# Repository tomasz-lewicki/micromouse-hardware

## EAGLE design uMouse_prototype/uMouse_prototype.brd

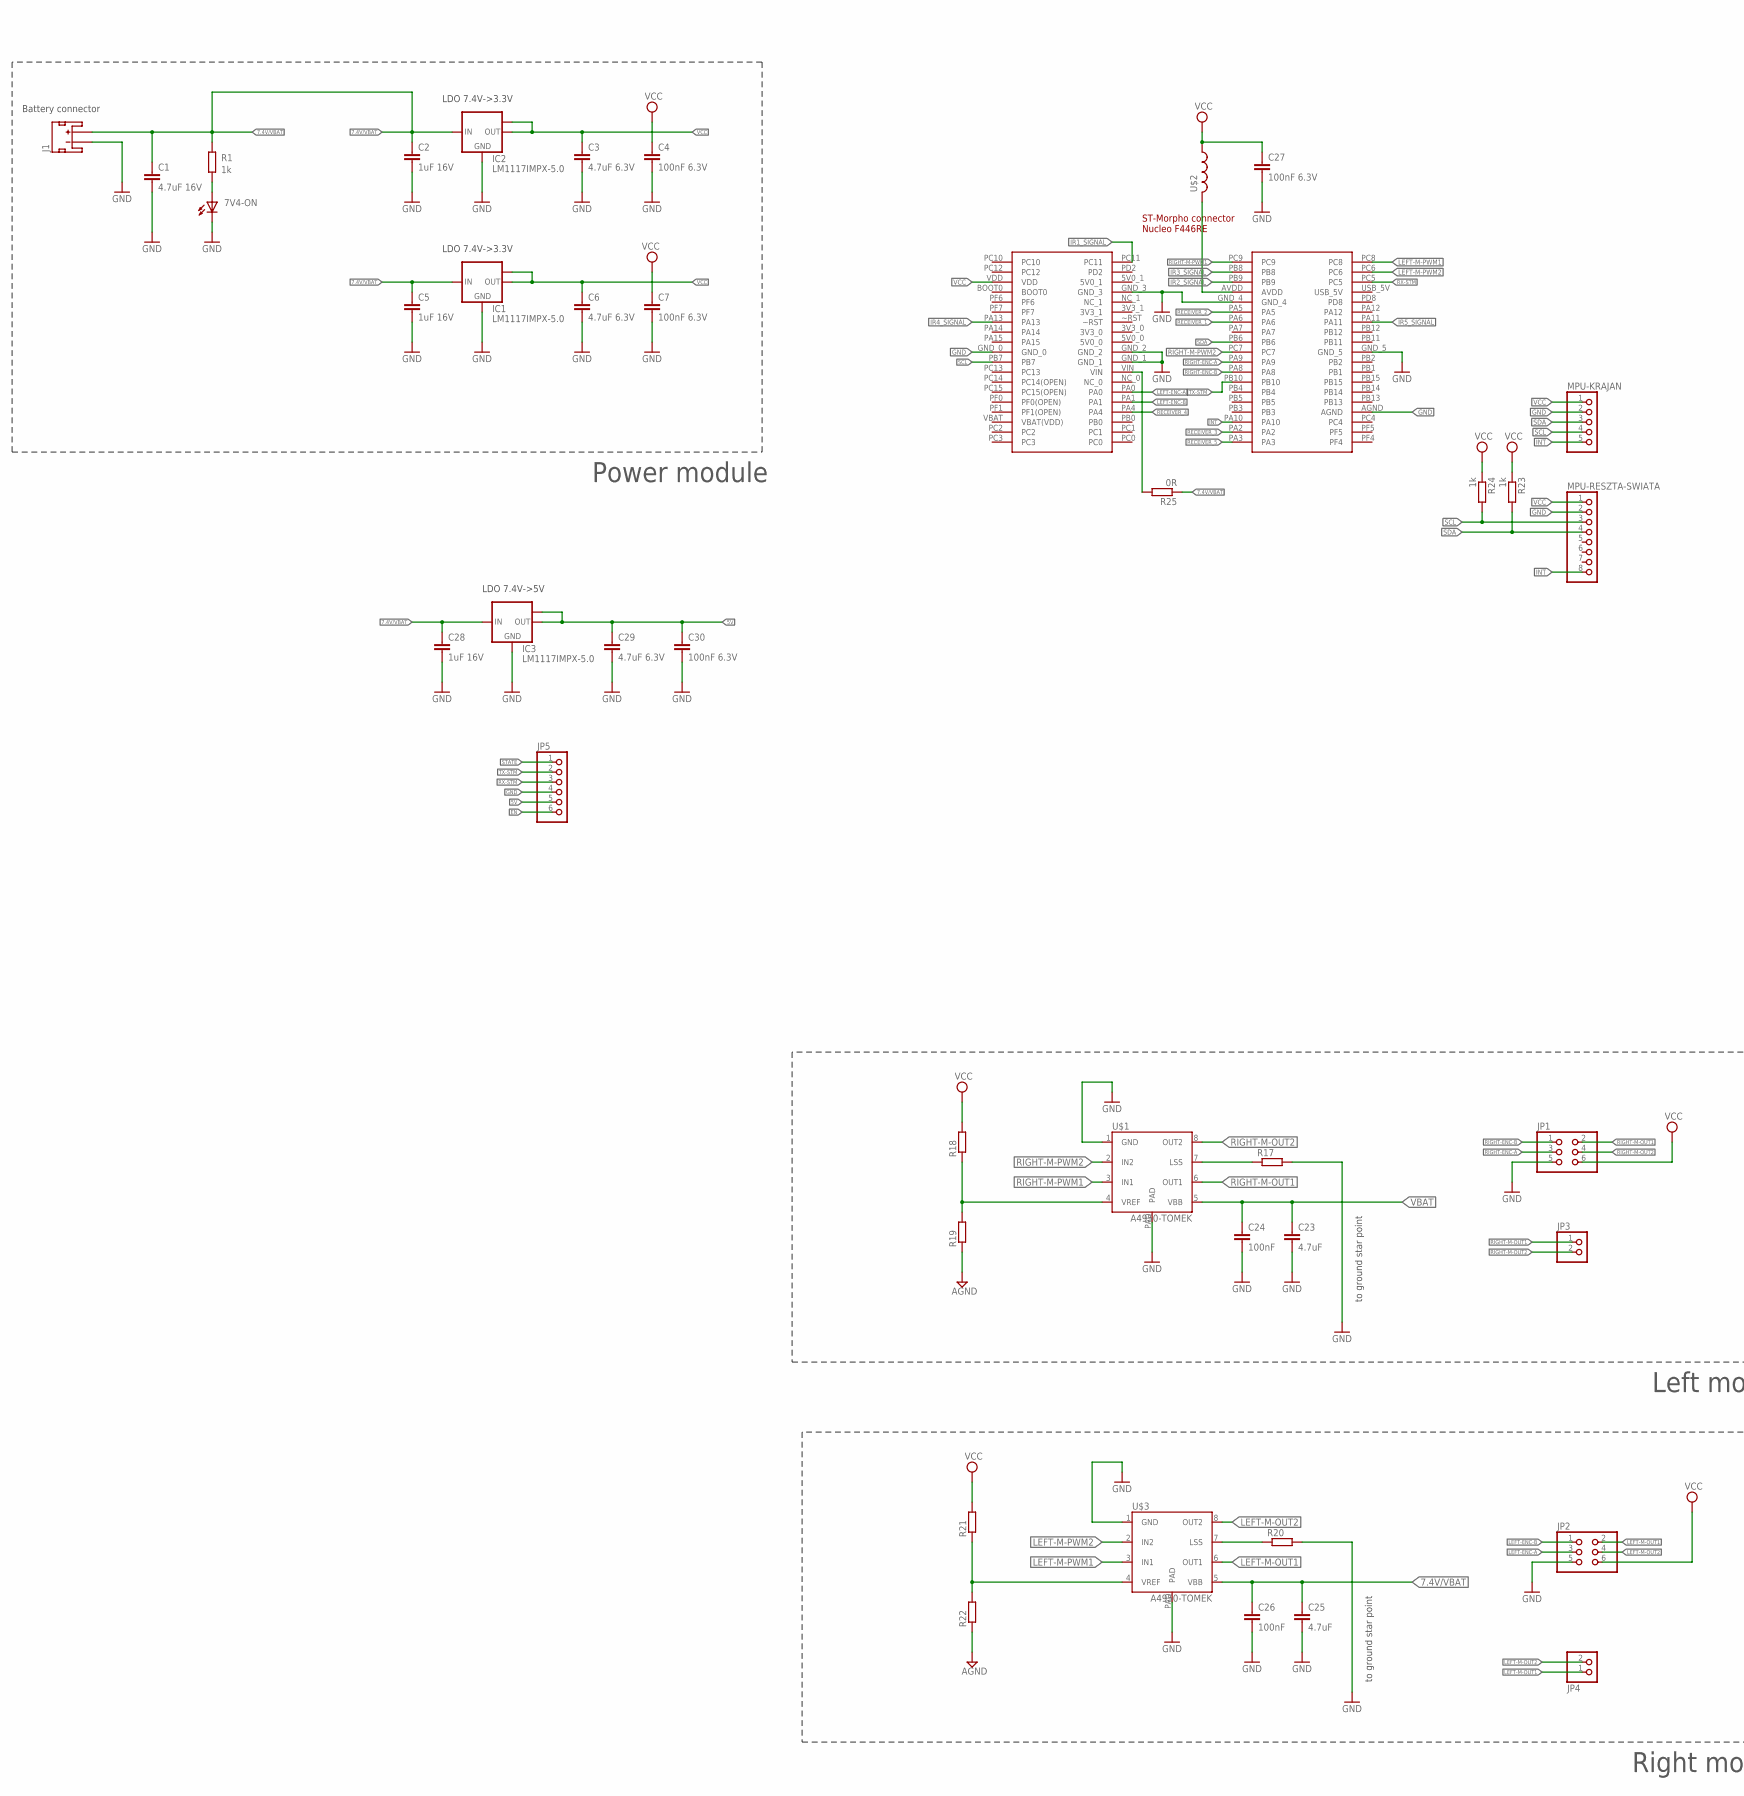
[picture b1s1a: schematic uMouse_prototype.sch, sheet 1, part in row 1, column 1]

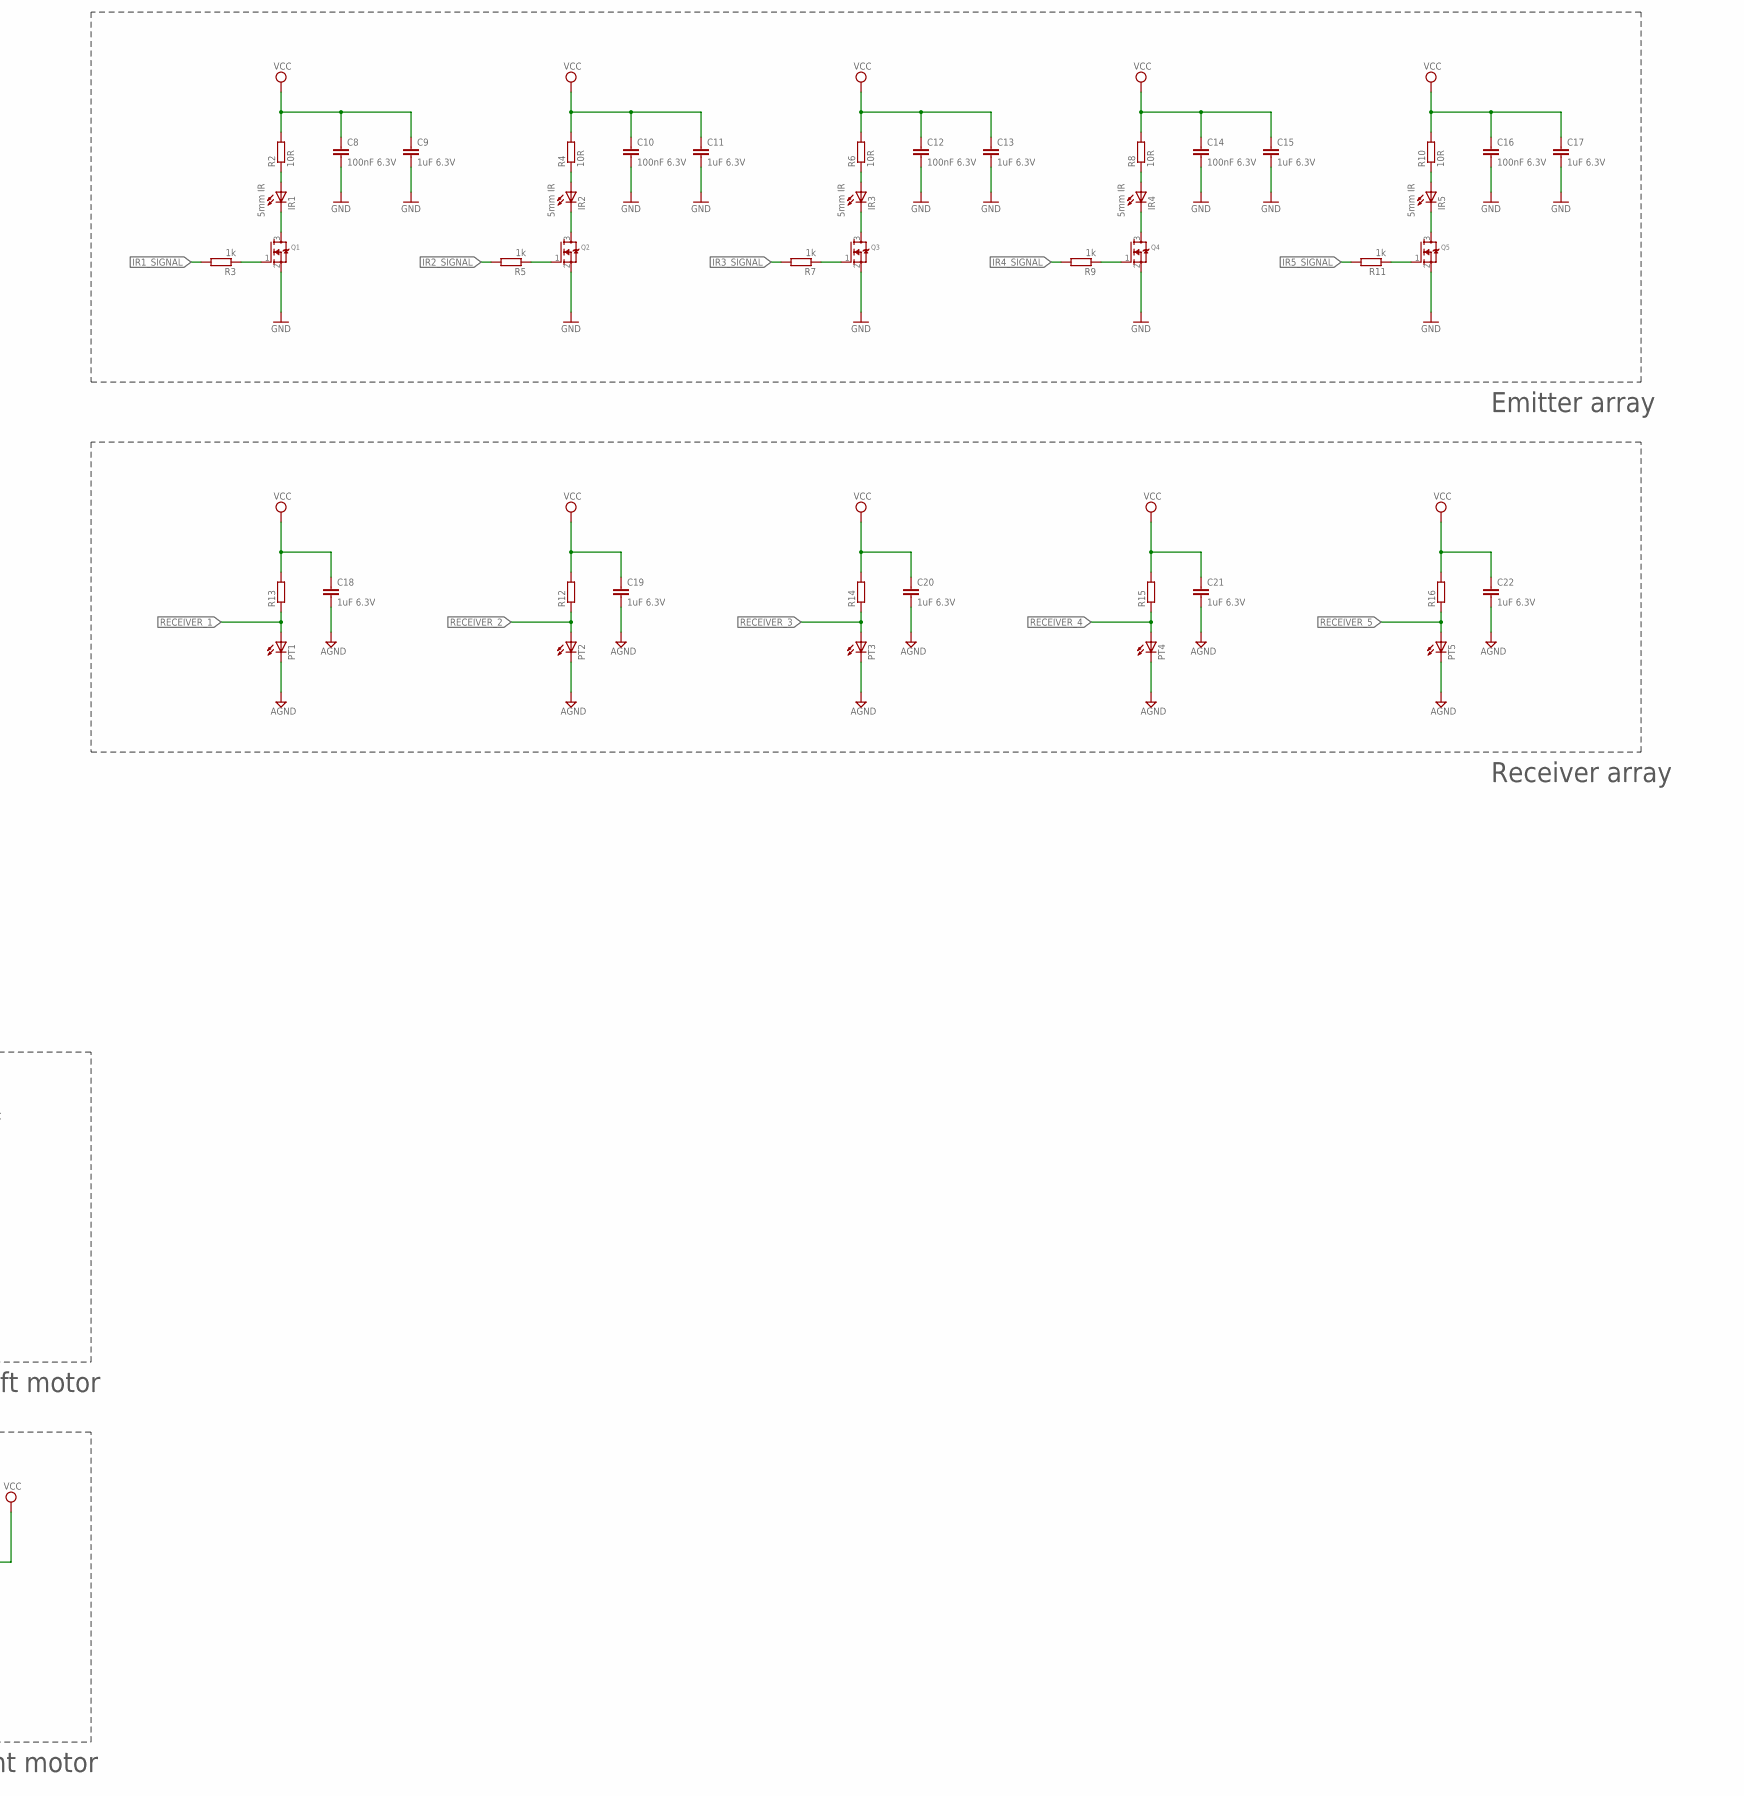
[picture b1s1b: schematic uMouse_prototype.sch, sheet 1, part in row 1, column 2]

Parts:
7V4-ON: LEDCHIP-LED0805; CHIP-LED0805
C1: 4.7uF 16V; C0805K
C2, C5, C28: 1uF 16V; C0805K
C3, C6, C29: 4.7uF 6.3V; C0805K
C4, C7, C8, C10, C12, C14, C16, C27, C30: 100nF 6.3V; C0805K
C9, C11, C13, C15, C17, C18, C19, C20, C21, C22: 1uF 6.3V; C0805K
C23, C25: 4.7uF; C0805K
C24, C26: 100nF; C0805K
IC1, IC2, IC3: LM1117IMPX-5.0; SOT223
IR1, IR2, IR3, IR4, IR5: 5mm IR; LED5MM
J1: JST_2MM_MALE; JST-2-SMD
JP1, JP2: PINHD-2X3; 2X03
JP3, JP4: PINHD-1X2; 1X02
JP5: PINHD-1X6; 1X06
MPU-KRAJAN: PINHD-1X5; 1X05
MPU-RESZTA-SWIATA: PINHD-1X8; 1X08
PT1, PT2, PT3, PT4, PT5: LED3MM
Q1, Q2, Q3, Q4, Q5: MOSFET-NREFLOW; SOT23
R1: 1k; R0805
R2, R4, R6, R8, R10: 10R; M0805
R3, R5, R7, R9, R11, R23, R24: 1k; M0805
R12, R13, R14, R15, R16, R18, R19, R21, R22: R-EU_R0805; R0805
R17, R20: R-EU_R2512; R2512
R25: 0R; M0805
U$1, U$3: A4950-TOMEK; SOIC8TP
U$2: INDUCTOR_0805_L; RESC0805_L
U$5: ST_MORPHO_STM32_F446RE; MORPHO-4X19

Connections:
5V: C29.1, C30.1, IC3.2 (OUT), IC3.TAB (OUT1), JP5.5
7.4V/VBAT: C1.1, C2.1, C5.1, C25.1, C26.1, C28.1, IC1.3 (IN), IC2.3 (IN), IC3.3 (IN), J1.2 (+), R1.2, R25.1, U$3.5 (VBB)
EN: JP5.6
GND: 7V4-ON.C, C1.2, C2.2, C3.2, C4.2, C5.2, C6.2, C7.2, C8.2, C9.2, C10.2, C11.2, C12.2, C13.2, C14.2, C15.2, C16.2, C17.2, C18.2, C19.2, C20.2, C21.2, C22.2, C23.2, C24.2, C25.2, C26.2, C27.2, C28.2, C29.2, C30.2, IC1.1 (GND), IC2.1 (GND), IC3.1 (GND), J1.1 (-), JP1.5, JP2.5, JP5.4, MPU-KRAJAN.2, MPU-RESZTA-SWIATA.2, PT1.K (C), PT2.K (C), PT3.K (C), PT4.K (C), PT5.K (C), Q1.2 (S), Q2.2 (S), Q3.2 (S), Q4.2 (S), Q5.2 (S), R17.2, R19.1, R20.2, R22.1, U$1.1 (GND), U$1.PAD, U$3.1 (GND), U$3.PAD, U$5.AGND, U$5.GND_0, U$5.GND_1, U$5.GND_2, U$5.GND_3, U$5.GND_4, U$5.GND_5
INT: MPU-KRAJAN.5, MPU-RESZTA-SWIATA.8, U$5.PA10
IR1_SIGNAL: R3.2, U$5.PC11
IR2_SIGNAL: R5.2, U$5.PB9
IR3: IR3.K (C), Q3.3 (D)
IR3_SIGNAL: R7.2, U$5.PB8
IR4_SIGNAL: R9.2, U$5.PA13
IR5_SIGNAL: R11.2, U$5.PA11
LEFT-ENC-A: JP2.3, U$5.PA0
LEFT-ENC-B: JP2.1, U$5.PA1
LEFT-M-OUT1: JP2.2, JP4.1, U$3.6 (OUT1)
LEFT-M-OUT2: JP2.4, JP4.2, U$3.8 (OUT2)
LEFT-M-PWM1: U$3.3 (IN1), U$5.PC8
LEFT-M-PWM2: U$3.2 (IN2), U$5.PC6
unnamed: 7V4-ON.A, R1.1
unnamed: Q1.1 (G), R3.1
unnamed: IR1.A, R2.1
unnamed: IR1.K (C), Q1.3 (D)
unnamed: Q2.1 (G), R5.1
unnamed: IR2.A, R4.1
unnamed: IR2.K (C), Q2.3 (D)
unnamed: Q3.1 (G), R7.1
unnamed: IR3.A, R6.1
unnamed: Q4.1 (G), R9.1
unnamed: IR4.A, R8.1
unnamed: IR4.K (C), Q4.3 (D)
unnamed: Q5.1 (G), R11.1
unnamed: IR5.A, R10.1
unnamed: IR5.K (C), Q5.3 (D)
unnamed: R17.1, U$1.7 (LSS)
unnamed: R18.1, R19.2, U$1.4 (VREF)
unnamed: R20.1, U$3.7 (LSS)
unnamed: R21.1, R22.2, U$3.4 (VREF)
unnamed: U$2.2, U$5.AVDD
unnamed: R25.2, U$5.VIN
RECEIVER_1: PT1.A, R13.1, U$5.PA6
RECEIVER_2: PT2.A, R12.1, U$5.PA5
RECEIVER_3: PT3.A, R14.1, U$5.PA2
RECEIVER_4: PT4.A, R15.1, U$5.PA4
RECEIVER_5: PT5.A, R16.1, U$5.PA3
RIGHT-ENC-A: JP1.3, U$5.PA9
RIGHT-ENC-B: JP1.1, U$5.PA8
RIGHT-M-OUT1: JP1.2, JP3.1, U$1.6 (OUT1)
RIGHT-M-OUT2: JP1.4, JP3.2, U$1.8 (OUT2)
RIGHT-M-PWM1: U$1.3 (IN1), U$5.PC9
RIGHT-M-PWM2: U$1.2 (IN2), U$5.PC7
RX-STM: JP5.3, U$5.PC5
SCL: MPU-KRAJAN.4, MPU-RESZTA-SWIATA.3, R24.2, U$5.PB7
SDA: MPU-KRAJAN.3, MPU-RESZTA-SWIATA.4, R23.2, U$5.PB6
STATE: JP5.1
TX-STM: JP5.2, U$5.PB10
VBAT: C23.1, C24.1, U$1.5 (VBB)
VCC: C3.1, C4.1, C6.1, C7.1, C8.1, C9.1, C10.1, C11.1, C12.1, C13.1, C14.1, C15.1, C16.1, C17.1, C18.1, C19.1, C20.1, C21.1, C22.1, C27.1, IC1.2 (OUT), IC1.TAB (OUT1), IC2.2 (OUT), IC2.TAB (OUT1), JP1.6, JP2.6, MPU-KRAJAN.1, MPU-RESZTA-SWIATA.1, R2.2, R4.2, R6.2, R8.2, R10.2, R12.2, R13.2, R14.2, R15.2, R16.2, R18.2, R21.2, R23.1, R24.1, U$2.1, U$5.VDD

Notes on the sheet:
Battery connector
LDO 7.4V->3.3V
Power module
Emitter array
Receiver array
to ground star point
Left motor
Right motor
LDO 7.4V->5V

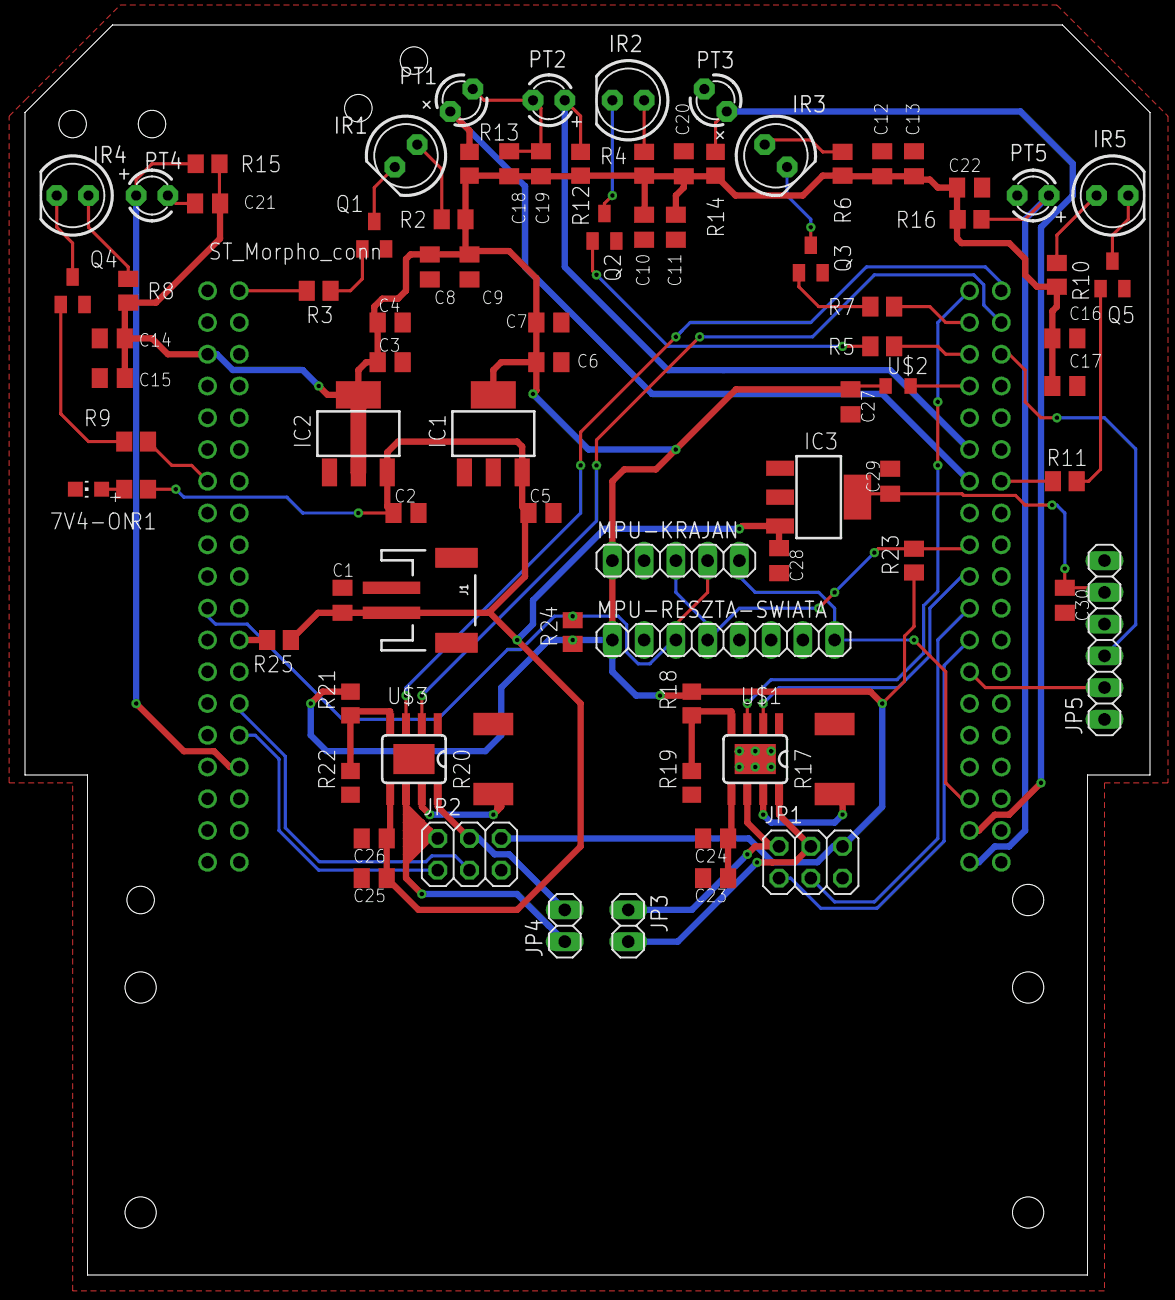
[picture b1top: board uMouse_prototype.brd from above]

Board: 2 copper layers, 90.0 x 100.0 mm, 86 parts (0 on the bottom side), 54 nets.

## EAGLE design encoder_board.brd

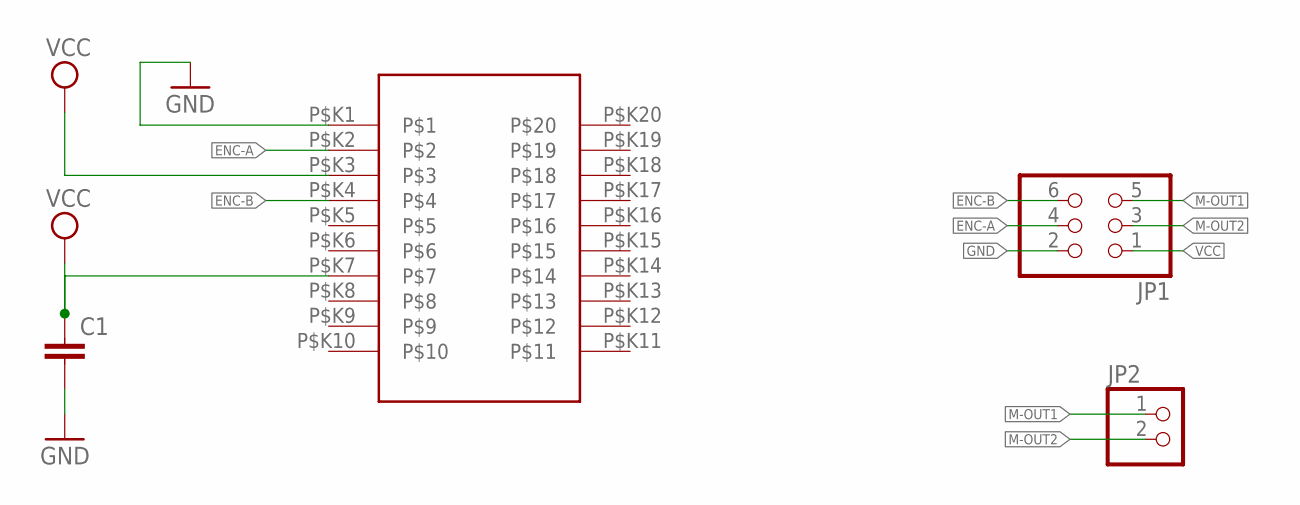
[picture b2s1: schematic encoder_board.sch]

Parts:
C1: C-EUC0805K; C0805K
JP1: PINHD-2X3; 2X03
JP2: PINHD-1X2; 1X02
U$1: TSSOP20

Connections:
ENC-A: JP1.4, U$1.P$K2
ENC-B: JP1.6, U$1.P$K4
GND: C1.2, JP1.2, U$1.P$K1
M-OUT1: JP1.5, JP2.1
M-OUT2: JP1.3, JP2.2
VCC: C1.1, JP1.1, U$1.P$K3, U$1.P$K7

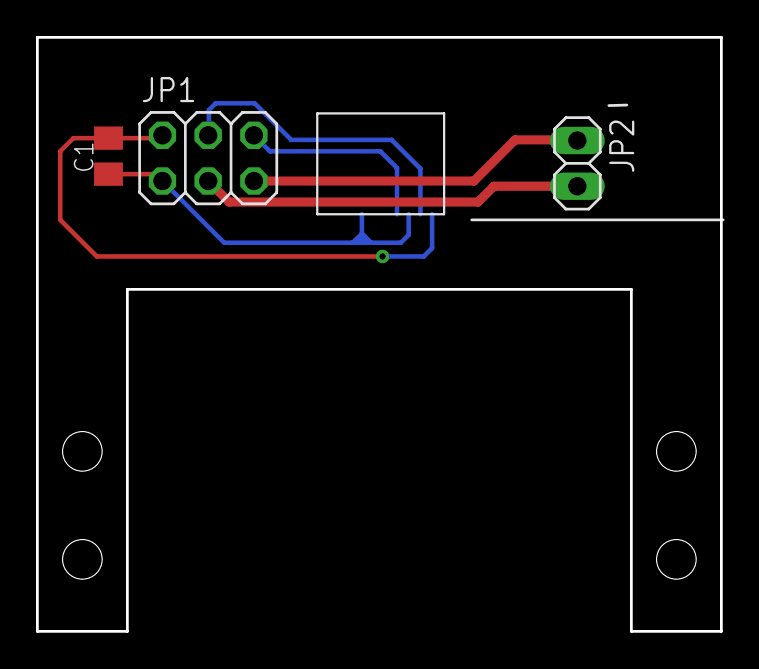
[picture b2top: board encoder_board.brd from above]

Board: 2 copper layers, 38.0 x 33.0 mm, 4 parts (1 on the bottom side), 6 nets.

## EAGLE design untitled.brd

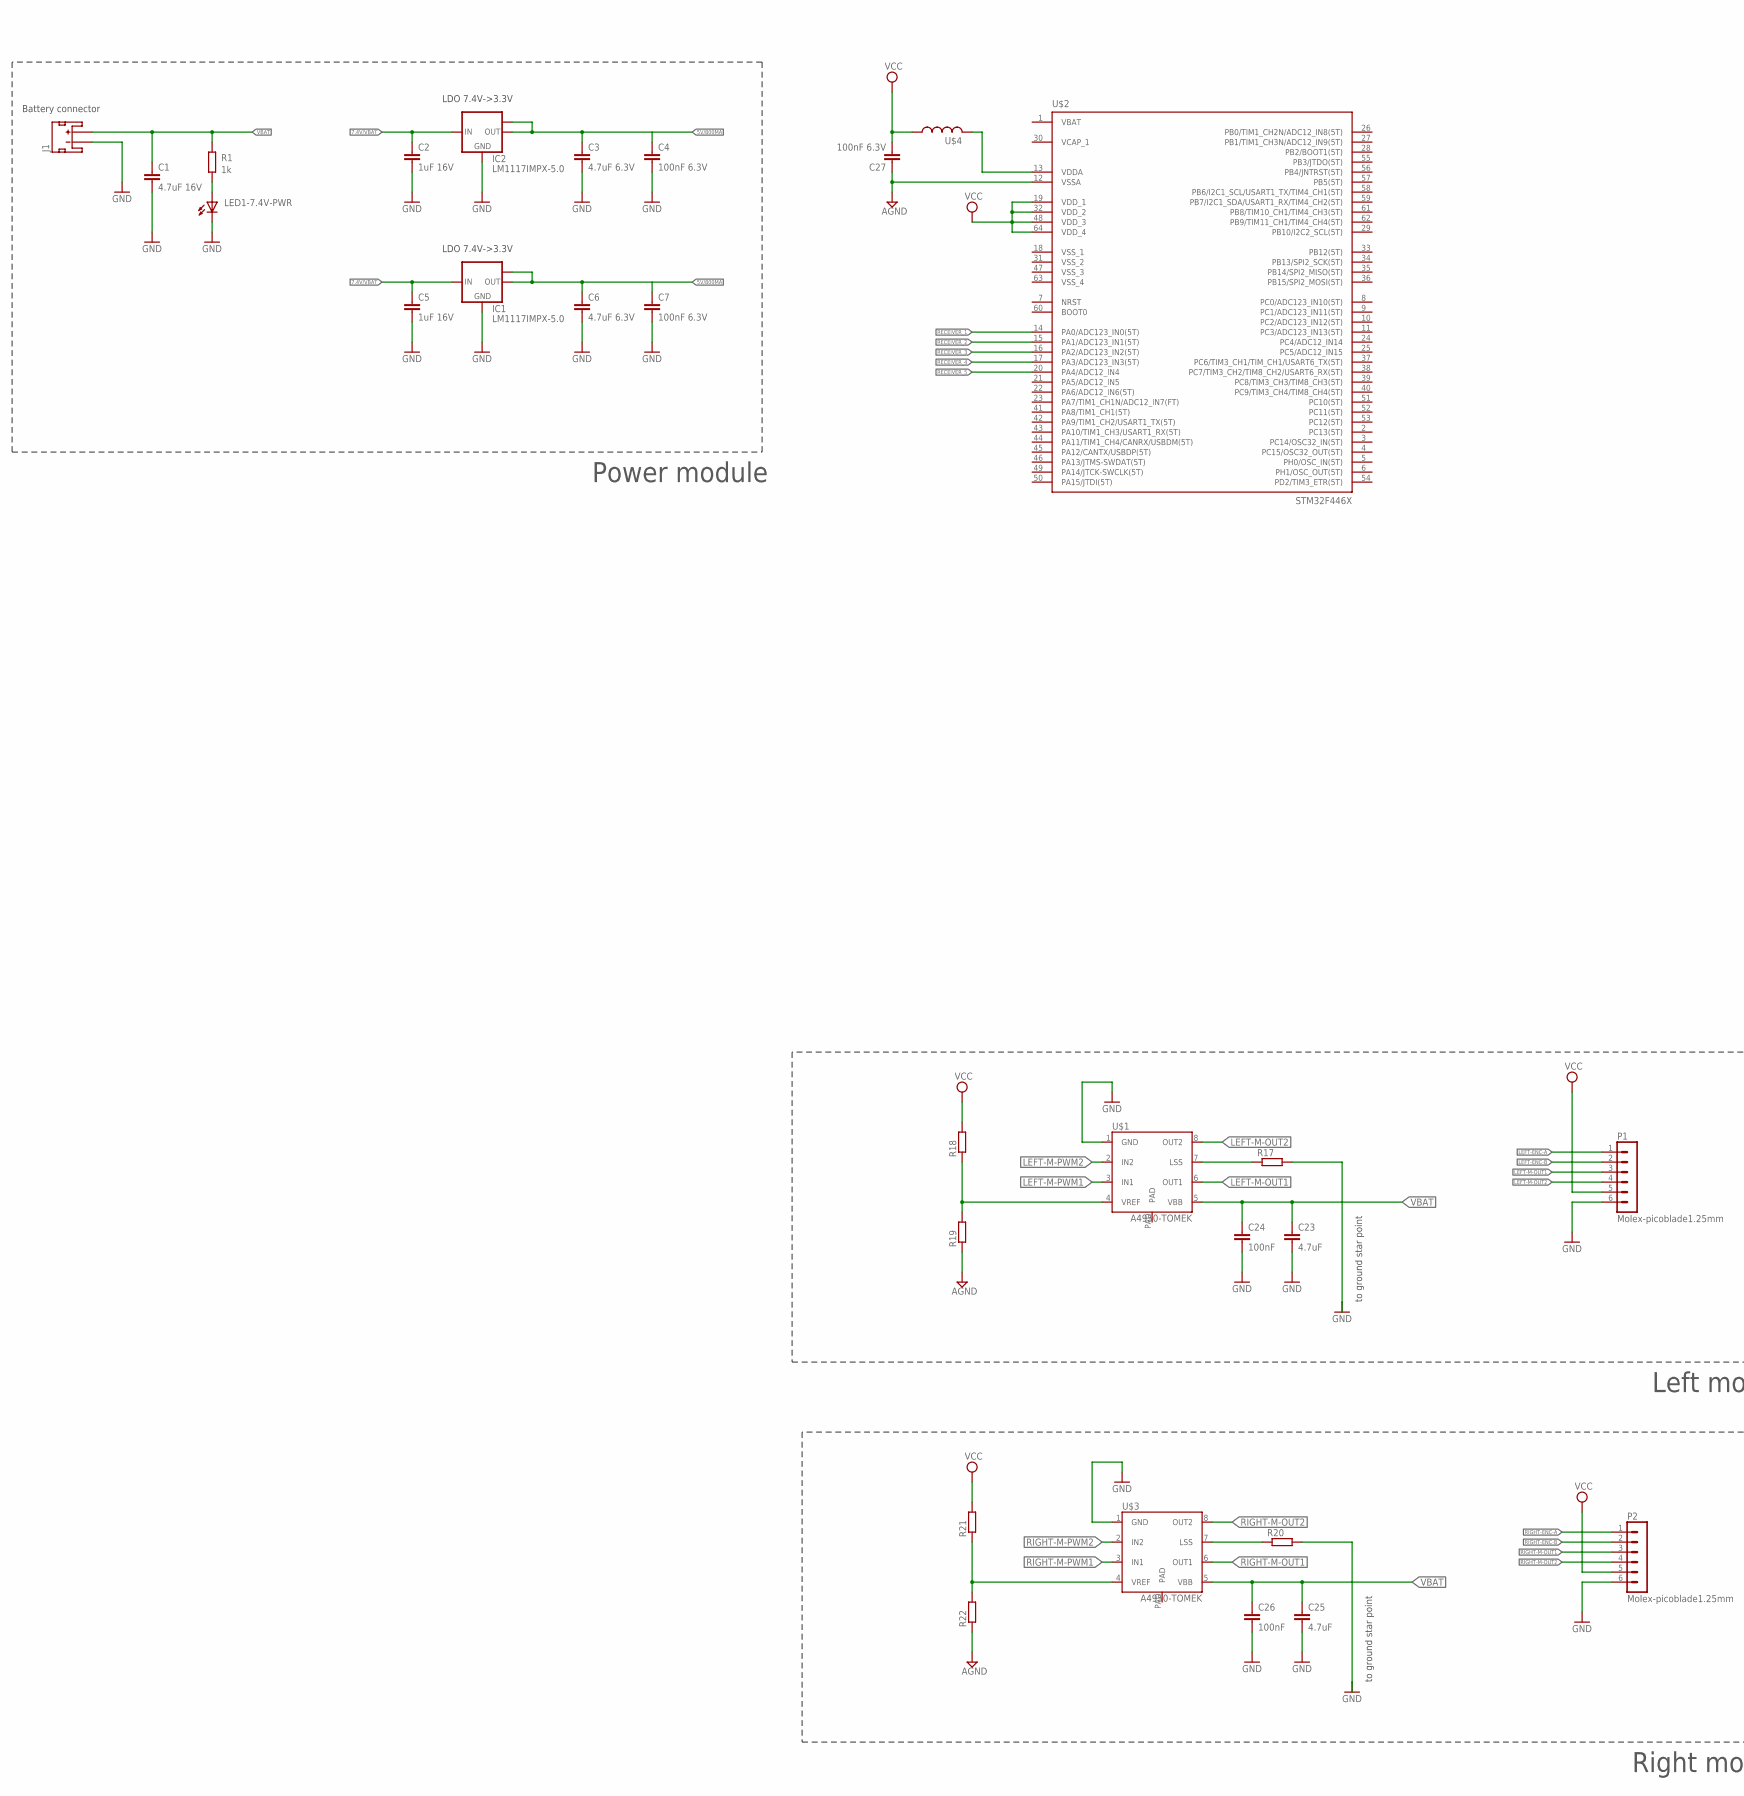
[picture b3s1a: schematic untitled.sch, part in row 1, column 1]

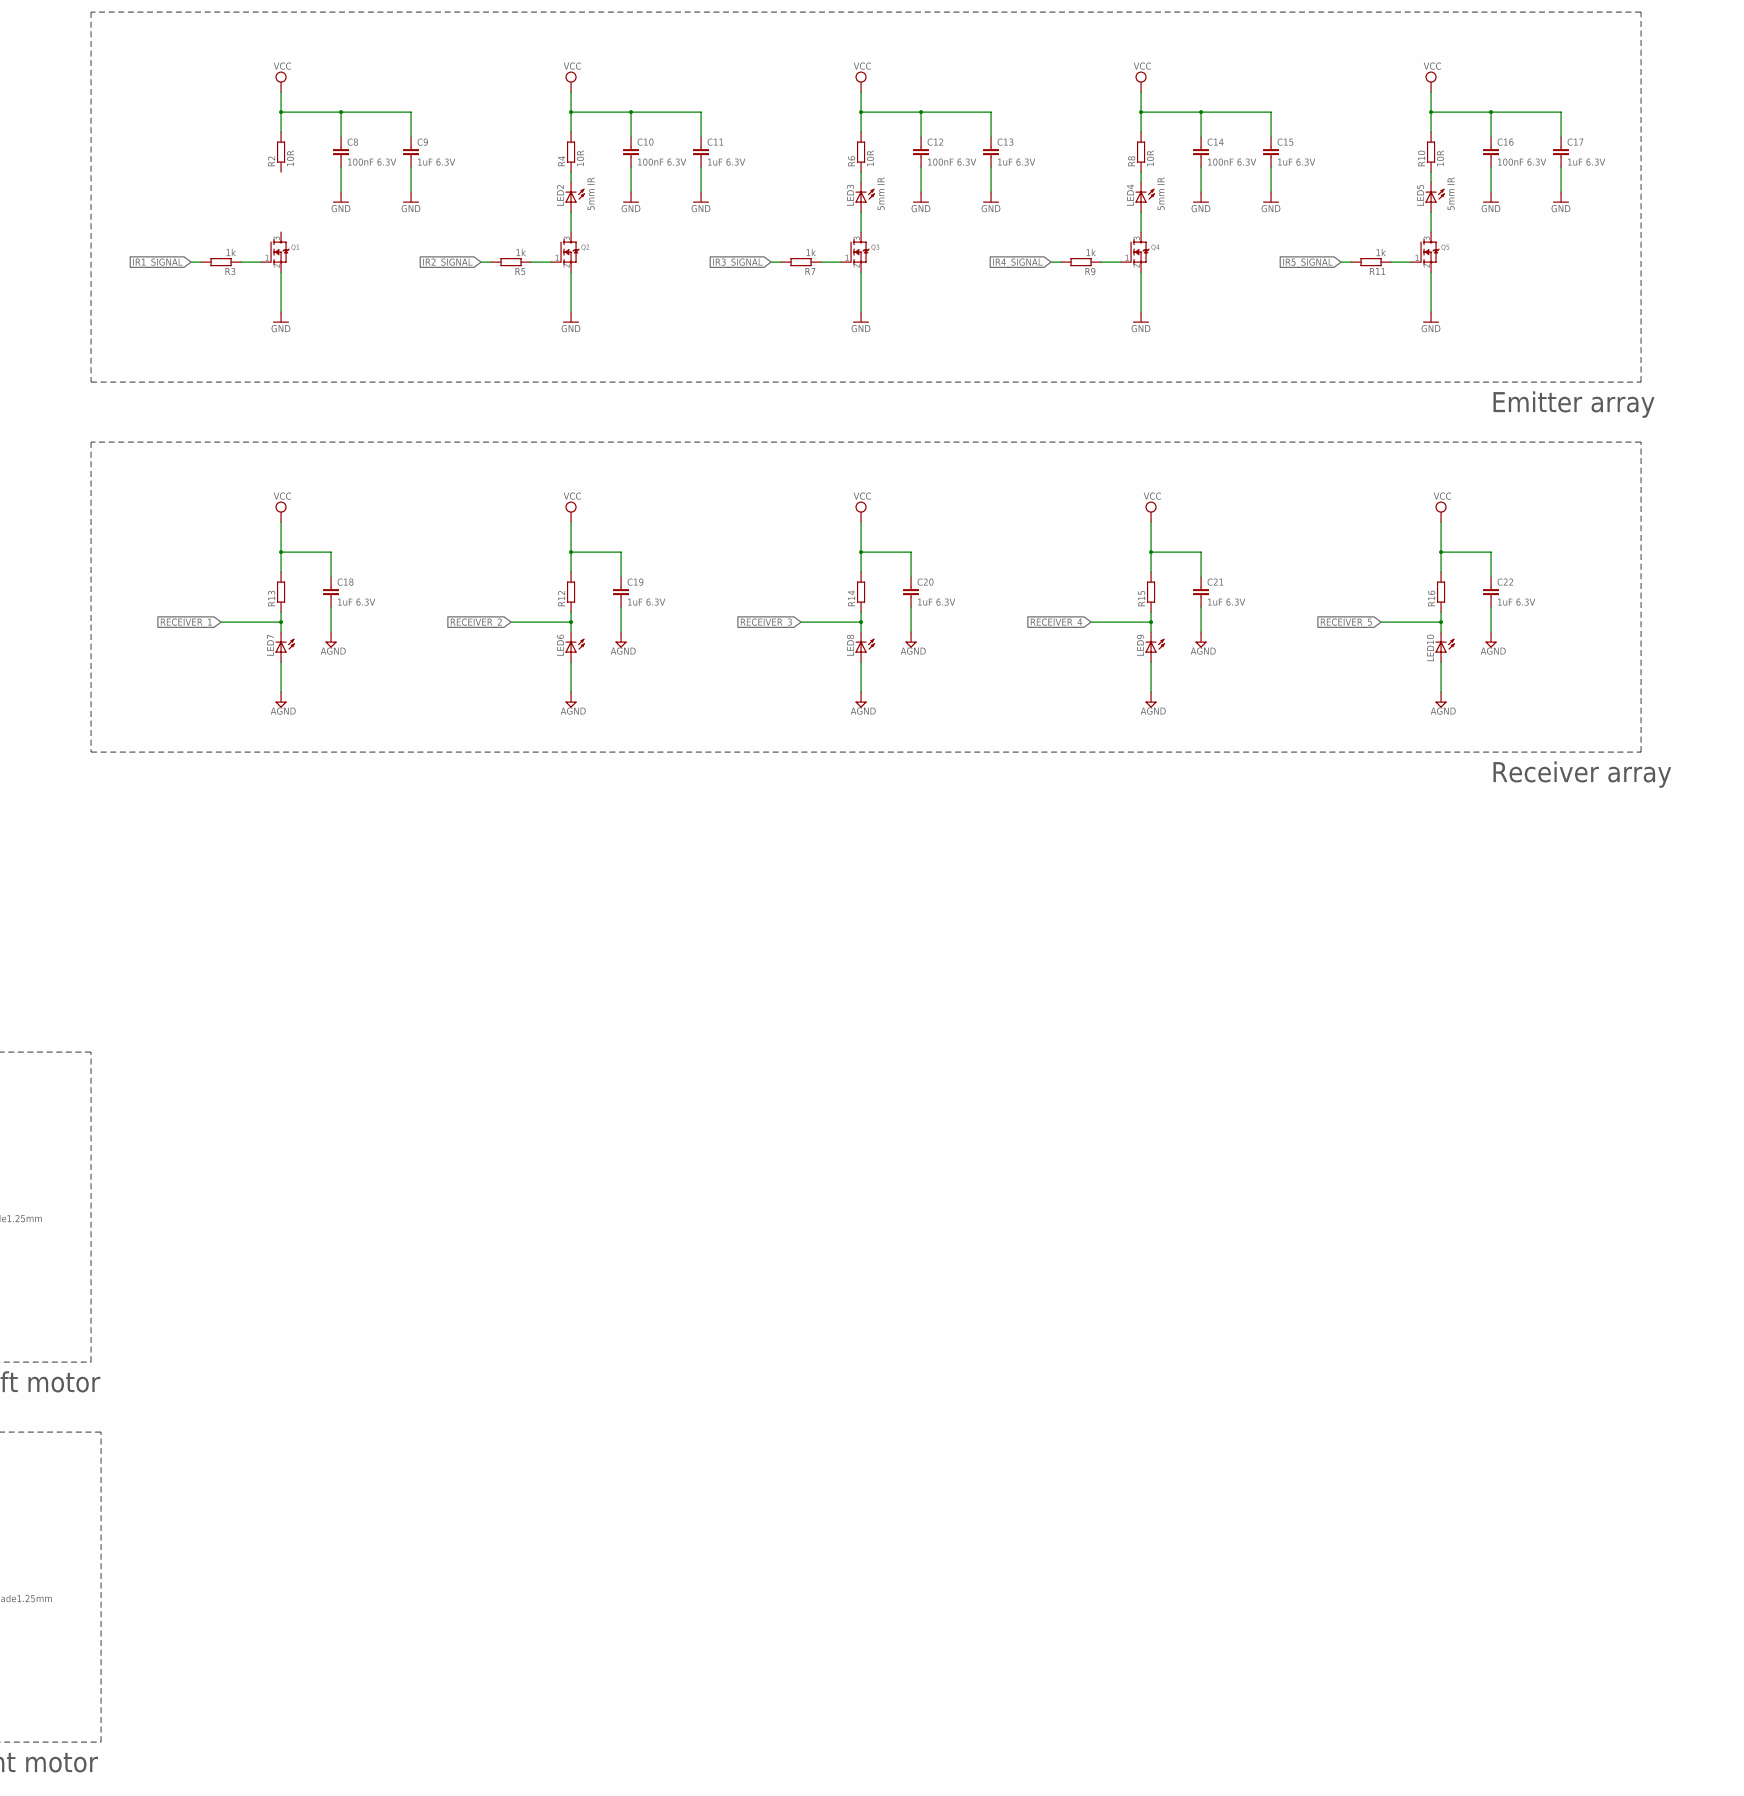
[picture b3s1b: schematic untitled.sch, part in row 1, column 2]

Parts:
C1: 4.7uF 16V; C0805K
C2, C5: 1uF 16V; C0805K
C3, C6: 4.7uF 6.3V; C0805K
C4, C7, C8, C10, C12, C14, C16, C27: 100nF 6.3V; C0805K
C9, C11, C13, C15, C17, C18, C19, C20, C21, C22: 1uF 6.3V; C0805K
C23, C25: 4.7uF; C0805K
C24, C26: 100nF; C0805K
IC1, IC2: LM1117IMPX-5.0; SOT223
J1: JST_2MM_MALE; JST-2-SMD
LED1-7.4V-PWR: LEDCHIP-LED0805; CHIP-LED0805
LED2, LED3, LED4, LED5: 5mm IR; LED5MM
LED6, LED7, LED8, LED9, LED10: LED5MM
P1, P2: Molex-picoblade1.25mm; 53398-0610
Q1, Q2, Q3, Q4, Q5: MOSFET-NREFLOW; SOT23
R1: 1k; R0805
R2, R4, R6, R8, R10: 10R; M0805
R3, R5, R7, R9, R11: 1k; M0805
R12, R13, R14, R15, R16, R18, R19, R21, R22: R-EU_R0805; R0805
R17, R20: R-EU_R2512; R2512
U$1, U$3: A4950-TOMEK; SOIC8TP
U$2: STM32F446X; TQFP64
U$4: INDUCTOR_0805_L; RESC0805_L

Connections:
5V/800MA: C3.1, C6.1, IC1.2 (OUT), IC1.TAB (OUT1), IC2.2 (OUT), IC2.TAB (OUT1)
5V/800MA1: C4.1
5V/800MA2: C7.1
7.4V/VBAT: C2.1, C5.1, IC1.3 (IN), IC2.3 (IN)
AGND: C18.2, C19.2, C20.2, C21.2, C22.2, C27.1, LED6.A, LED7.A, LED8.A, LED9.A, LED10.A, R19.1, R22.1, U$2.12 (VSSA)
GND: C1.2, C2.2, C3.2, C4.2, C5.2, C6.2, C7.2, C8.2, C9.2, C10.2, C11.2, C12.2, C13.2, C14.2, C15.2, C16.2, C17.2, C23.2, C24.2, C25.2, C26.2, IC1.1 (GND), IC2.1 (GND), J1.1 (-), LED1-7.4V-PWR.C, P1.6, P2.6, Q1.2 (S), Q2.2 (S), Q3.2 (S), Q4.2 (S), Q5.2 (S), R17.2, R20.2, U$1.1 (GND), U$3.1 (GND)
IR1_SIGNAL: R3.2
IR2_SIGNAL: R5.2
IR3_SIGNAL: R7.2
IR4_SIGNAL: R9.2
IR5_SIGNAL: R11.2
LEFT-ENC-A: P1.1
LEFT-ENC-B: P1.2
LEFT-M-OUT1: P1.3, U$1.6 (OUT1)
LEFT-M-OUT2: P1.4, U$1.8 (OUT2)
LEFT-M-PWM1: U$1.3 (IN1)
LEFT-M-PWM2: U$1.2 (IN2)
unnamed: LED1-7.4V-PWR.A, R1.1
unnamed: Q1.1 (G), R3.1
unnamed: Q2.1 (G), R5.1
unnamed: LED2.A, Q2.3 (D)
unnamed: LED2.K (C), R4.1
unnamed: Q3.1 (G), R7.1
unnamed: LED3.A, Q3.3 (D)
unnamed: LED3.K (C), R6.1
unnamed: Q4.1 (G), R9.1
unnamed: LED4.A, Q4.3 (D)
unnamed: LED4.K (C), R8.1
unnamed: Q5.1 (G), R11.1
unnamed: LED5.A, Q5.3 (D)
unnamed: LED5.K (C), R10.1
unnamed: R17.1, U$1.7 (LSS)
unnamed: R18.1, R19.2, U$1.4 (VREF)
unnamed: R20.1, U$3.7 (LSS)
unnamed: R21.1, R22.2, U$3.4 (VREF)
unnamed: U$2.13 (VDDA), U$4.2
RECEIVER_1: LED7.K (C), R13.1, U$2.14 (PA0/ADC123_IN0(5T))
RECEIVER_2: LED6.K (C), R12.1, U$2.15 (PA1/ADC123_IN1(5T))
RECEIVER_3: LED8.K (C), R14.1, U$2.16 (PA2/ADC123_IN2(5T))
RECEIVER_4: LED9.K (C), R15.1, U$2.17 (PA3/ADC123_IN3(5T))
RECEIVER_5: LED10.K (C), R16.1, U$2.20 (PA4/ADC12_IN4)
RIGHT-ENC-A: P2.1
RIGHT-ENC-B: P2.2
RIGHT-M-OUT1: P2.3, U$3.6 (OUT1)
RIGHT-M-OUT2: P2.4, U$3.8 (OUT2)
RIGHT-M-PWM1: U$3.3 (IN1)
RIGHT-M-PWM2: U$3.2 (IN2)
VBAT: C1.1, C23.1, C24.1, C25.1, C26.1, J1.2 (+), R1.2, U$1.5 (VBB), U$3.5 (VBB)
VCC: C8.1, C9.1, C10.1, C11.1, C12.1, C13.1, C14.1, C15.1, C16.1, C17.1, C18.1, C19.1, C20.1, C21.1, C22.1, C27.2, P1.5, P2.5, R2.2, R4.2, R6.2, R8.2, R10.2, R12.2, R13.2, R14.2, R15.2, R16.2, R18.2, R21.2, U$2.19 (VDD_1), U$2.32 (VDD_2), U$2.48 (VDD_3), U$2.64 (VDD_4), U$4.1

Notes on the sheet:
Battery connector
LDO 7.4V->3.3V
Power module
Emitter array
Receiver array
to ground star point
Left motor
Right motor

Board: 2 copper layers, 73 parts (0 on the bottom side), 34 nets, no tracks yet.

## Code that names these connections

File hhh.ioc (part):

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Mcu.Name=STM32F446R(C-E)Tx
Mcu.Package=LQFP64
Mcu.UserName=STM32F446RETx
PA0-WKUP.Signal=S_TIM2_CH1_ETR
PA1.Signal=S_TIM2_CH2
PA10.Signal=S_TIM1_CH3
PA11.Signal=GPIO_Output
PA13.Signal=GPIO_Output
PA2.Signal=ADCx_IN2
PA3.Signal=ADCx_IN3
PA4.Signal=ADCx_IN4
PA5.Signal=ADCx_IN5
PA6.Signal=ADCx_IN6
PA8.Signal=S_TIM1_CH1
PA9.Signal=S_TIM1_CH2
PB10.Mode=Asynchronous
PB10.Signal=USART3_TX
PB6.Mode=I2C
PB6.Signal=I2C1_SCL
PB7.Mode=I2C
PB7.Signal=I2C1_SDA
PB8.Signal=GPIO_Output
PB9.Signal=GPIO_Output
PC11.Signal=GPIO_Output
PC5.Mode=Asynchronous
PC5.Signal=USART3_RX
PC6.Signal=S_TIM8_CH1
PC7.Signal=S_TIM8_CH2
PC8.Signal=S_TIM8_CH3
PC9.Signal=S_TIM8_CH4

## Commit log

2017-11-09 added first schematic
2017-12-10 synchronizacja do stanu ze skype
2017-12-10 added libraries used
2017-12-21 zmienione konektroy na IDC, fototranzystory na 3mm, zasilanie 7.4V podpiete do Vin nucleo, zmieniony rozmiar plyty, wszystkie PWM-y od silnika podpiete do tim8, niektore sygnaly od IR zostaly ODPIETE.
2017-12-21 usunalem stare pliki
2017-12-24 plytka zlayoutowana, pozostaje zrobic polaczenia
2017-12-26 gotowa, czeka na uwagi Tomka i Kuby
2017-12-28 ostatnie poprawki, plytka do enkoderow
2017-12-29 poprawione i2c, dodane otwory pod holderki do ledów IR (tylko przy dwóch)
2017-12-29 gerbery dla enkoderow
2017-12-29 dodane gerbery do glownej plyty prototypu
2017-12-30 dodane gerbery dla duzej plyty
2017-12-30 wyrzucone śmieci, wszystkie pliki są teraz w folderach

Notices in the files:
parts and their libraries:
SparkFun-Connectors: Licensing: Creative Commons ShareAlike 4.0 International - https://creativecommons.org/licenses/by-sa/4.0
molex-pico: Copyright (C) 2010, Bob Starr
